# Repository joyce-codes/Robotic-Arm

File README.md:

# Bionic Robotic Arm
## Description
The ultimate open-source blueprint for human augmentation, engineered for solo makers. This repository contains everything a single developer needs to build a fully functional, automated bionic arm from scratch using standard desktop tools. From high-fidelity EMG muscle-activity sensor schematics and custom controller motherboards to print-ready 3D CAD models for the hand and arm architecture, every piece of hardware is optimized for independent fabrication. Driven by an intuitive, low-latency core software suite for real-time signal processing, this project turns complex cybernetics into an accessible, end-to-end weekend build you can execute entirely on your own.

## Objectives of the project
Create a construction of the arm(with hand), needed electronic like the muscle sensors, controller and software that will be able to properly control the mechanism depending on the signals received from the muscles.

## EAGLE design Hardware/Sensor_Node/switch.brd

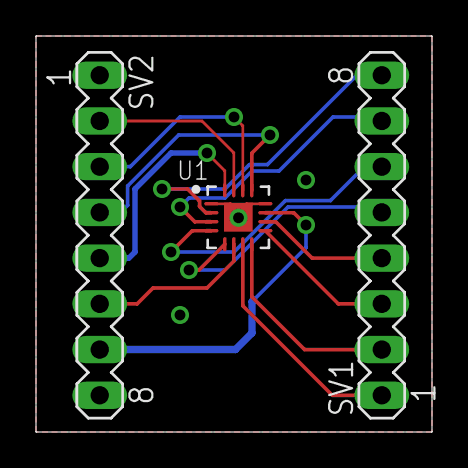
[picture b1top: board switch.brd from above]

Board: 2 copper layers, 22.0 x 22.0 mm, 4 parts (1 on the bottom side), 15 nets.

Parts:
C1: C0805
SV1, SV2: MA08-1
U1: ANALOG_DEVICES_ADG1608BCPZ-REEL7ANALOG_DEVICES_AD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; ANALOG_DEVICES_ADG1608BCPZ-REEL7_1

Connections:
GND: C1.2, SV2.1, SV2.8, U1.1, U1.12, U1.17
unnamed: SV2.5, U1.16
unnamed: SV1.8, U1.2
unnamed: SV2.6, U1.6
unnamed: SV2.2, U1.15
unnamed: SV2.3, U1.14
unnamed: SV2.4, U1.13
unnamed: SV1.7, U1.3
unnamed: SV1.6, U1.4
unnamed: SV1.5, U1.5
unnamed: SV1.4, U1.10
unnamed: SV1.3, U1.9
unnamed: SV1.2, U1.8
unnamed: SV1.1, U1.7
VCC: C1.1, SV2.7, U1.11
